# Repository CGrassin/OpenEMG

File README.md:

# OpenEMG

Electromyography (EMG) is a commonly used electrodiagnostic medicine technique for evaluating and recording the electrical activity produced by skeletal muscles. OpenEMG is a project that aims to create an open-source, easy-to-make EMG module that can capture muscle information from Arduino or any other micro-controller. With this module, users can measure muscle activity and use the data to explore various applications such as robotics and prosthetics.

View the article about this project (including performance, usage, principle of operation) here: https://charleslabs.fr/en/project-OpenEMG+Arduino+Sensor

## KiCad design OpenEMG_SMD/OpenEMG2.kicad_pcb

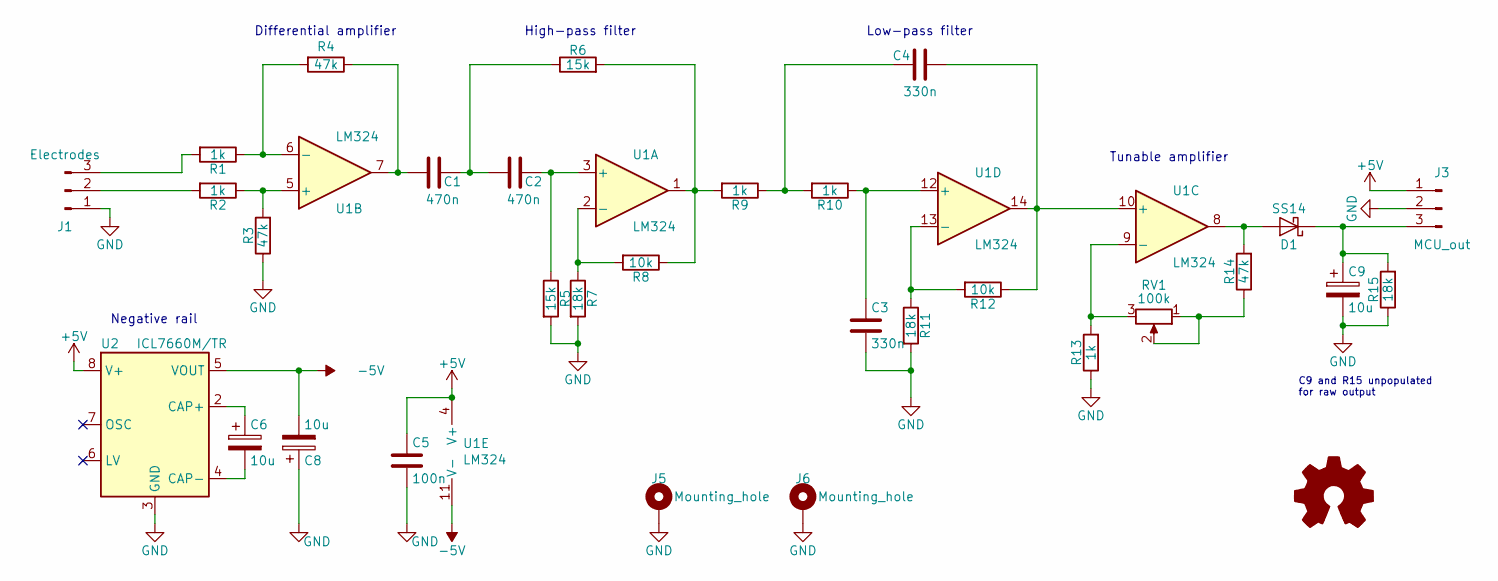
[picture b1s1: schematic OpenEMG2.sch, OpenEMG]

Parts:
C1, C2: 470n; C_0805_2012Metric
C3, C4: 330n; C_0805_2012Metric
C5: 100n; C_0805_2012Metric
C6, C8, C9: 10u; CP_Elec_6.3x4.5
D1: SS14; D_SMA
J1: Electrodes; PinHeader_1x03_P2.54mm_Vertical
J3: MCU_out; PinHeader_1x03_P2.54mm_Vertical
J5, J6: Mounting_hole; MountingHole_2.2mm_M2_DIN965_Pad
LOGO1: logo
R1, R2, R9, R10, R13: 1k; R_0805_2012Metric
R3, R4, R14: 47k; R_0805_2012Metric
R5, R6: 15k; R_0805_2012Metric
R7, R11, R15: 18k; R_0805_2012Metric
R8, R12: 10k; R_0805_2012Metric
RV1: 100k; Potentiometer_Bourns_TC33X_Vertical
U1: LM324; SOIC-14_3.9x8.7mm_P1.27mm
U2: ICL7660M/TR; SOP-8_3.76x4.96mm_P1.27mm

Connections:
+5V: C5.1, J3.1, U1.4 (V+), U2.8 (V+)
-5V: C8.2, U1.11 (V-), U2.5 (VOUT)
GND: C3.2, C5.2, C8.1, C9.2, J1.1, J3.2, J5.1, J6.1, R3.1, R5.2, R7.2, R11.2, R13.1, R15.1, U2.3 (GND)
unnamed: C1.1, C2.2, R6.1
unnamed: C1.2, R4.1, U1.7
unnamed: C2.1, R5.1, U1.3 (+)
unnamed: C3.1, R10.1, U1.12 (+)
unnamed: C4.1, R9.1, R10.2
unnamed: C4.2, R12.1, U1.10 (+), U1.14
unnamed: C6.1, U2.2 (CAP+)
unnamed: C6.2, U2.4 (CAP-)
unnamed: C9.1, D1.1 (K), J3.3, R15.2
unnamed: D1.2 (A), R14.2, U1.8
unnamed: J1.2, R2.2
unnamed: J1.3, R1.2
unnamed: R1.1, R4.2, U1.6 (-)
unnamed: R2.1, R3.2, U1.5 (+)
unnamed: R6.2, R8.1, R9.2, U1.1
unnamed: R7.1, R8.2, U1.2 (-)
unnamed: R11.1, R12.2, U1.13 (-)
unnamed: R13.2, RV1.3, U1.9 (-)
unnamed: R14.1, RV1.1, RV1.2

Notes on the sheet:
Differential amplifier
Tunable amplifier
High-pass filter
Low-pass filter
Negative rail
C9 and R15 unpopulated for raw output

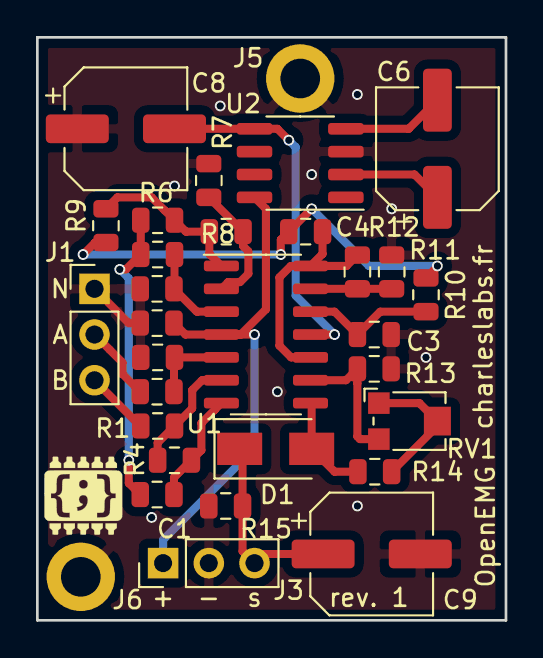
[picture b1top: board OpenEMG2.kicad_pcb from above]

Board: 2 copper layers, 26.0 x 32.4 mm, 32 parts (0 on the bottom side), 22 nets.
